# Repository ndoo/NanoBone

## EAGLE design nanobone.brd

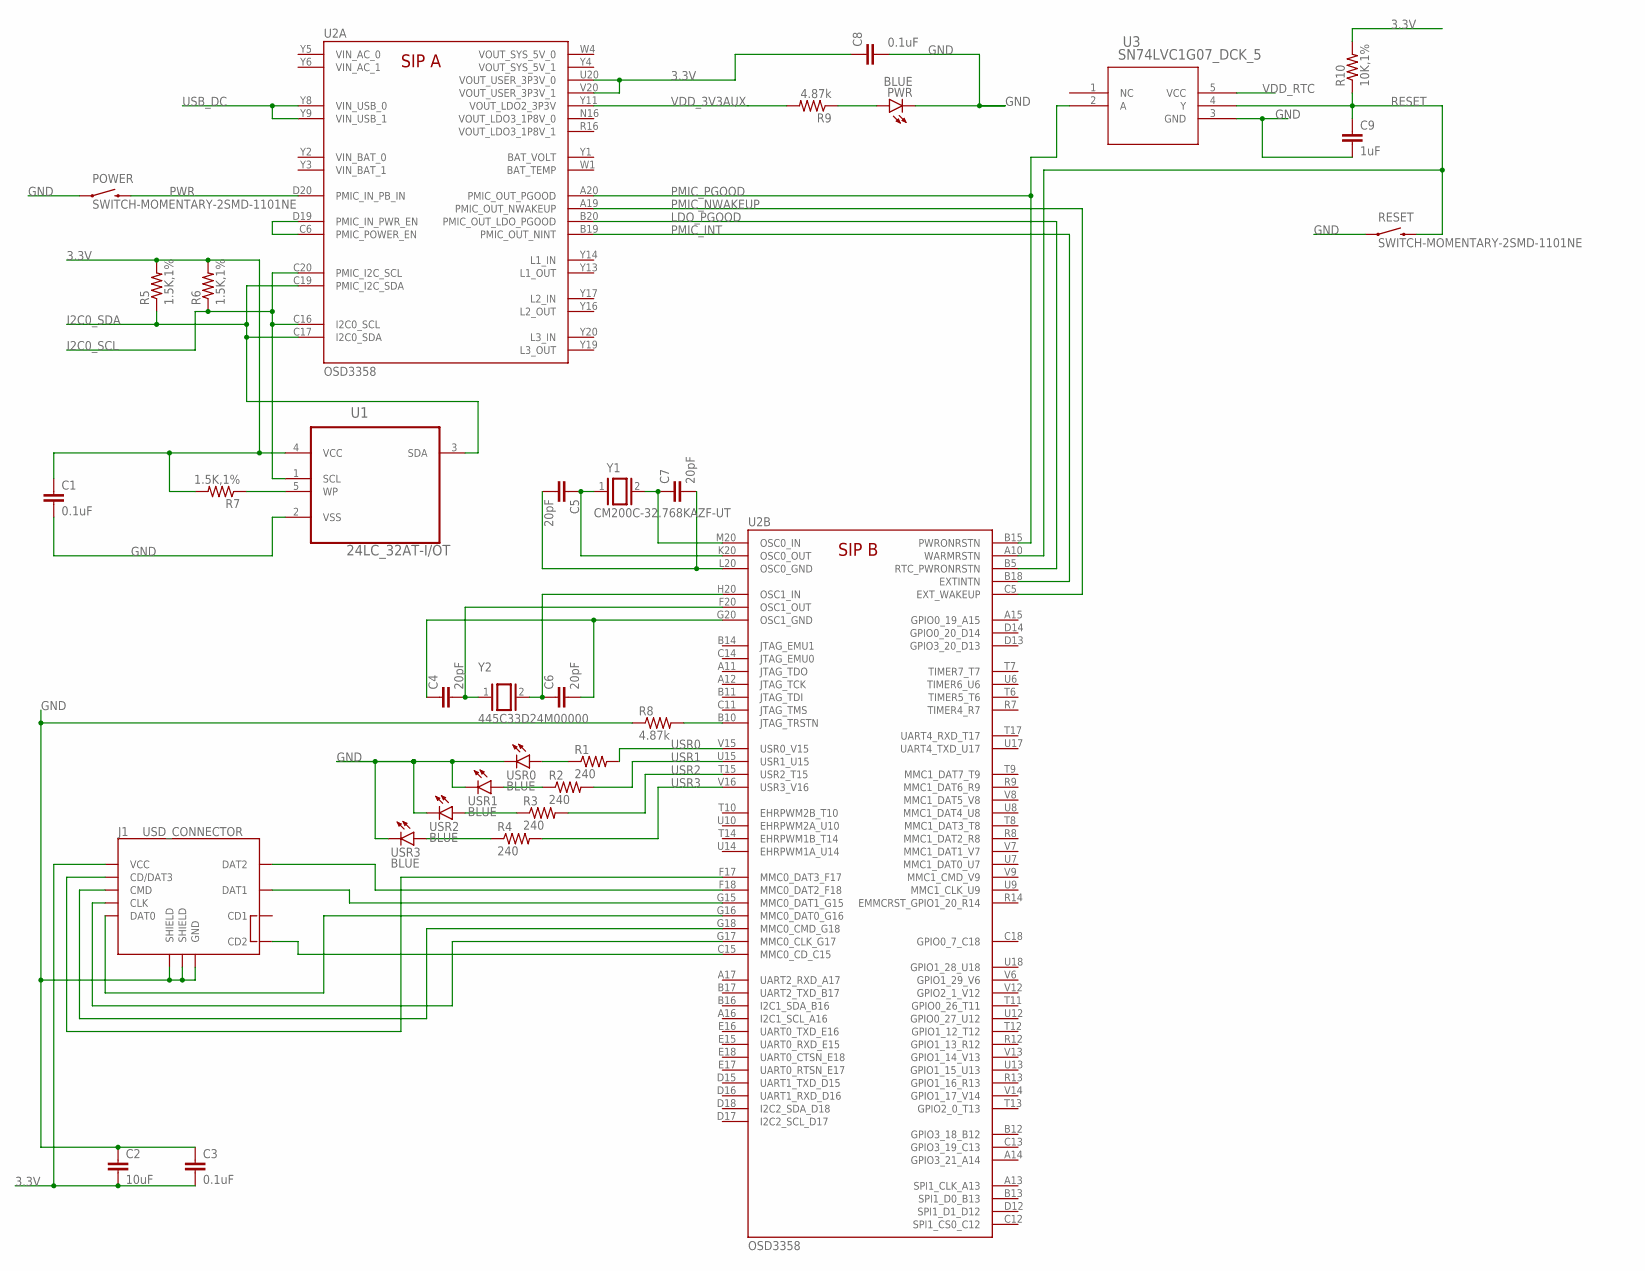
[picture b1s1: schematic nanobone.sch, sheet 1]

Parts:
C1, C3, C8: 0.1uF; 0402-CAP
C2: 10uF; 0805
C4, C5, C6, C7: 20pF; 0402-CAP
C9: 1uF; 0402-CAP
J1: USD_CONNECTOR; MICRO-SD-SOCKET-PP
POWER: SWITCH-MOMENTARY-2SMD-1101NE; TACTILE-SWITCH-1101NE
PWR: BLUE; 0402-LED
R1, R2, R3, R4: 240; 0402-RES
R5, R6, R7: 1.5K,1%; 0402-RES
R8, R9: 4.87k; 0402-RES
R10: 10K,1%; 0402-RES
RESET: SWITCH-MOMENTARY-2SMD-1101NE; TACTILE-SWITCH-1101NE
U1: 24LC_32AT-I/OT; SOT95P290X145-5N
U2: OSD3358
U3: SN74LVC1G07_DCK_5; DCK5
USR0, USR1, USR2, USR3: BLUE; 0402-LED
Y1: CM200C-32.768KAZF-UT
Y2: 445C33D24M00000

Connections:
3.3V: C1.1, C2.2, C3.2, C8.1, J1.VCC, R5.2, R6.2, R7.2, R10.2, U1.4 (VCC), U2.U20 (VOUT_USER_3P3V_0), U2.V20 (VOUT_USER_3P3V_1); also elsewhere on the board
GND: C1.2, C2.1, C3.1, C8.2, C9.2, J1.GND, J1.GND1 (SHIELD), J1.GND3 (SHIELD), POWER.1, PWR.C, R8.1, RESET.1, U1.2 (VSS), U3.3 (GND), USR0.C, USR1.C, USR2.C, USR3.C; also elsewhere on the board
I2C0_SCL: R6.1, U1.1 (SCL), U2.C16 (I2C0_SCL), U2.C20 (PMIC_I2C_SCL)
I2C0_SDA: R5.1, U1.3 (SDA), U2.C17 (I2C0_SDA), U2.C19 (PMIC_I2C_SDA)
LDO_PGOOD: U2.B5 (RTC_PWRONRSTN), U2.B20 (PMIC_OUT_LDO_PGOOD)
unnamed: J1.CLK, U2.G17 (MMC0_CLK_G17)
unnamed: J1.CD/DAT3, U2.F17 (MMC0_DAT3_F17)
unnamed: R8.2, U2.B10 (JTAG_TRSTN)
unnamed: R1.1, USR0.A
unnamed: R2.1, USR1.A
unnamed: R3.1, USR2.A
unnamed: R4.1, USR3.A
unnamed: U2.C6 (PMIC_POWER_EN), U2.D19 (PMIC_IN_PWR_EN)
unnamed: PWR.A, R9.1
unnamed: C7.1, U2.M20 (OSC0_IN), Y1.2
unnamed: C5.1, U2.K20 (OSC0_OUT), Y1.1
unnamed: R7.1, U1.5 (WP)
unnamed: C5.2, C7.2, U2.L20 (OSC0_GND)
unnamed: C6.1, U2.H20 (OSC1_IN), Y2.2
unnamed: C4.2, U2.F20 (OSC1_OUT), Y2.1
unnamed: C4.1, C6.2, U2.G20 (OSC1_GND)
unnamed: J1.DAT1, U2.G15 (MMC0_DAT1_G15)
unnamed: J1.CMD, U2.G18 (MMC0_CMD_G18)
unnamed: J1.CD2, U2.C15 (MMC0_CD_C15)
unnamed: J1.DAT0, U2.G16 (MMC0_DAT0_G16)
NTE: J1.DAT2, U2.F18 (MMC0_DAT2_F18)
PMIC_INT: U2.B18 (EXTINTN), U2.B19 (PMIC_OUT_NINT)
PMIC_NWAKEUP: U2.A19 (PMIC_OUT_NWAKEUP), U2.C5 (EXT_WAKEUP)
PMIC_PGOOD: U2.A20 (PMIC_OUT_PGOOD), U2.B15 (PWRONRSTN), U3.2 (A)
PWR: POWER.2, U2.D20 (PMIC_IN_PB_IN)
RESET: C9.1, R10.1, RESET.2, U2.A10 (WARMRSTN), U3.4 (Y)
USB_DC: U2.Y8 (VIN_USB_0), U2.Y9 (VIN_USB_1); also elsewhere on the board
USR0: R1.2, U2.V15 (USR0_V15)
USR1: R2.2, U2.U15 (USR1_U15)
USR2: R3.2, U2.T15 (USR2_T15)
USR3: R4.2, U2.V16 (USR3_V16)
VDD_3V3AUX: R9.2, U2.Y11 (VOUT_LDO2_3P3V)
VDD_RTC: U3.5 (VCC); also elsewhere on the board
VIN_AC_0: U2.Y5 (VIN_AC_0)
VIN_AC_1: U2.Y6 (VIN_AC_1)
VIN_BAT_0: U2.Y2 (VIN_BAT_0)
VIN_BAT_1: U2.Y3 (VIN_BAT_1)
VOUT_LDO3_1P8V_0: U2.N16 (VOUT_LDO3_1P8V_0)
VOUT_LDO3_1P8V_1: U2.R16 (VOUT_LDO3_1P8V_1)
VOUT_SYS_5V_0: U2.W4 (VOUT_SYS_5V_0)
VOUT_SYS_5V_1: U2.Y4 (VOUT_SYS_5V_1)

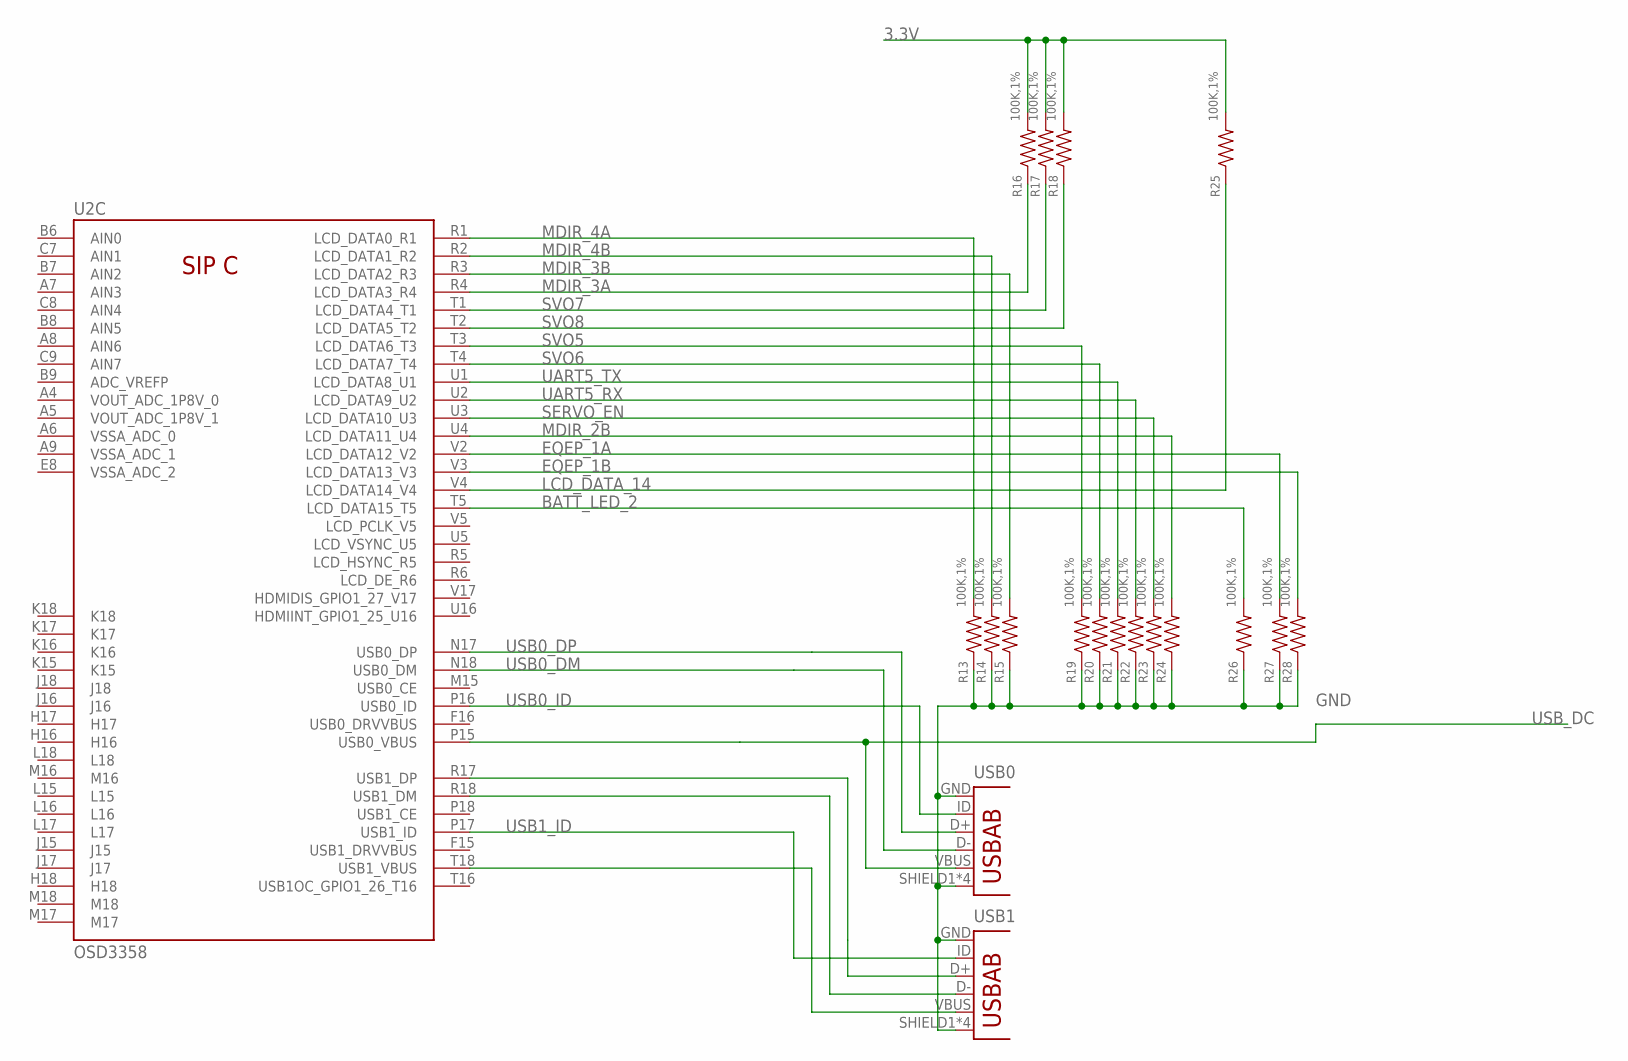
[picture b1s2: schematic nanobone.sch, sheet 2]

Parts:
R13, R14, R15, R16, R17, R18, R19, R20, R21, R22, R23, R24, R25, R26, R27, R28: 100K,1%; 0402-RES
U2: OSD3358
USB0, USB1: USB-AB; USB-AB-MICRO-SMD

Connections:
3.3V: R16.2, R17.2, R18.2, R25.2; also elsewhere on the board
BATT_LED_2: R26.2, U2.T5 (LCD_DATA15_T5)
EQEP_1A: R27.2, U2.V2 (LCD_DATA12_V2)
EQEP_1B: R28.2, U2.V3 (LCD_DATA13_V3)
GND: R13.1, R14.1, R15.1, R19.1, R20.1, R21.1, R22.1, R23.1, R24.1, R26.1, R27.1, R28.1, USB0.GND, USB0.SHIELD1 (SHIELD), USB0.SHIELD2 (SHIELD), USB0.SHIELD3 (SHIELD), USB0.SHIELD4 (SHIELD), USB1.GND, USB1.SHIELD1 (SHIELD), USB1.SHIELD2 (SHIELD), USB1.SHIELD3 (SHIELD), USB1.SHIELD4 (SHIELD); also elsewhere on the board
LCD_DATA_14: R25.1, U2.V4 (LCD_DATA14_V4)
MDIR_2B: R24.2, U2.U4 (LCD_DATA11_U4)
MDIR_3A: R16.1, U2.R4 (LCD_DATA3_R4)
MDIR_3B: R15.2, U2.R3 (LCD_DATA2_R3)
MDIR_4A: R13.2, U2.R1 (LCD_DATA0_R1)
MDIR_4B: R14.2, U2.R2 (LCD_DATA1_R2)
unnamed: U2.R17 (USB1_DP), USB1.D+
unnamed: U2.R18 (USB1_DM), USB1.D-
unnamed: U2.T18 (USB1_VBUS), USB1.VBUS
SERVO_EN: R23.2, U2.U3 (LCD_DATA10_U3)
SVO5: R19.2, U2.T3 (LCD_DATA6_T3)
SVO6: R20.2, U2.T4 (LCD_DATA7_T4)
SVO7: R17.1, U2.T1 (LCD_DATA4_T1)
SVO8: R18.1, U2.T2 (LCD_DATA5_T2)
UART5_RX: R22.2, U2.U2 (LCD_DATA9_U2)
UART5_TX: R21.2, U2.U1 (LCD_DATA8_U1)
USB0_DM: U2.N18 (USB0_DM), USB0.D-
USB0_DP: U2.N17 (USB0_DP), USB0.D+
USB0_ID: U2.P16 (USB0_ID), USB0.ID (USBID)
USB1_ID: U2.P17 (USB1_ID), USB1.ID (USBID)
USB_DC: U2.P15 (USB0_VBUS), USB0.VBUS; also elsewhere on the board
VIN_AC_0: U2.Y5 (VIN_AC_0)
VIN_AC_1: U2.Y6 (VIN_AC_1)
VIN_BAT_0: U2.Y2 (VIN_BAT_0)
VIN_BAT_1: U2.Y3 (VIN_BAT_1)
VOUT_LDO3_1P8V_0: U2.N16 (VOUT_LDO3_1P8V_0)
VOUT_LDO3_1P8V_1: U2.R16 (VOUT_LDO3_1P8V_1)
VOUT_SYS_5V_0: U2.W4 (VOUT_SYS_5V_0)
VOUT_SYS_5V_1: U2.Y4 (VOUT_SYS_5V_1)

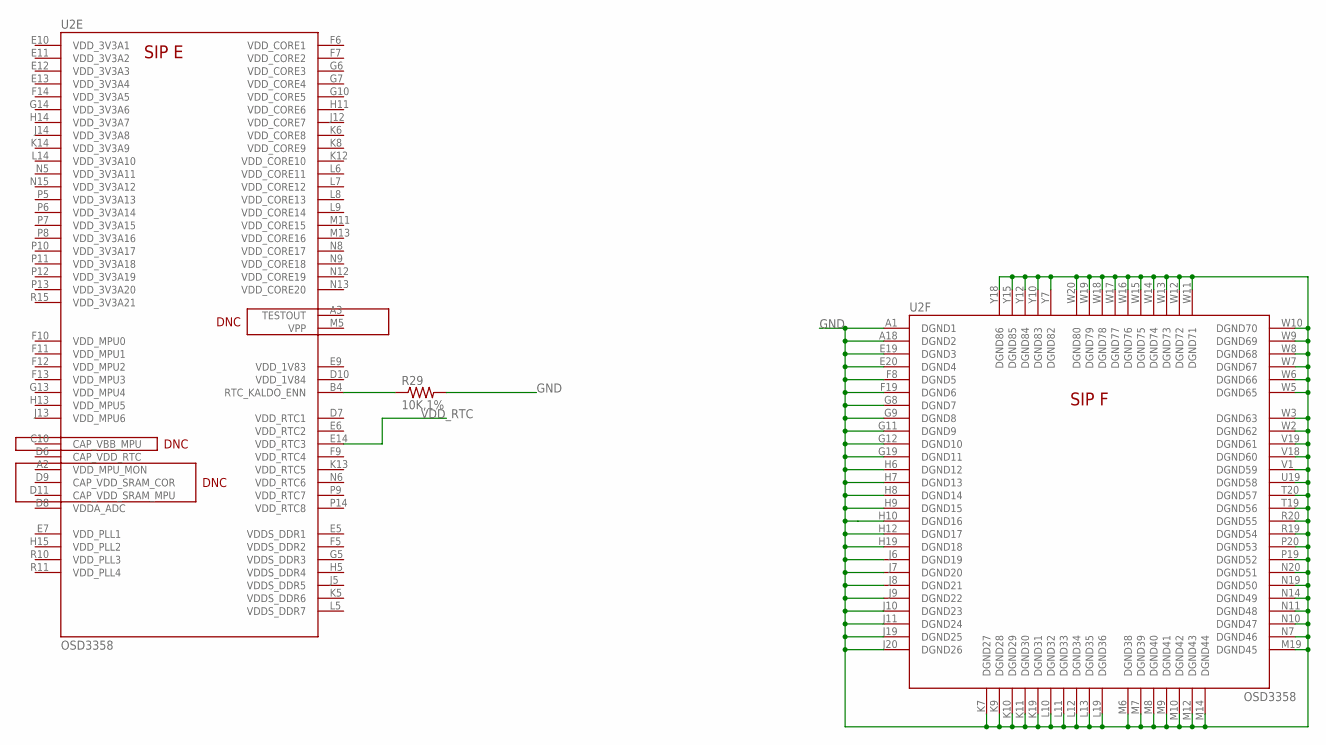
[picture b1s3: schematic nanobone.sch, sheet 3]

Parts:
R29: 10K,1%; 0402-RES
U2: OSD3358

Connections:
GND: R29.2, U2.A1 (DGND1), U2.A18 (DGND2), U2.E19 (DGND3), U2.E20 (DGND4), U2.F8 (DGND5), U2.F19 (DGND6), U2.G8 (DGND7), U2.G9 (DGND8), U2.G11 (DGND9), U2.G12 (DGND10), U2.G19 (DGND11), U2.H6 (DGND12), U2.H7 (DGND13), U2.H8 (DGND14), U2.H9 (DGND15), U2.H10 (DGND16), U2.H12 (DGND17), U2.H19 (DGND18), U2.J6 (DGND19), U2.J7 (DGND20), U2.J8 (DGND21), U2.J9 (DGND22), U2.J10 (DGND23), U2.J11 (DGND24), U2.J19 (DGND25), U2.J20 (DGND26), U2.K7 (DGND27), U2.K9 (DGND28), U2.K10 (DGND29), U2.K11 (DGND30), U2.K19 (DGND31), U2.L10 (DGND32), U2.L11 (DGND33), U2.L12 (DGND34), U2.L13 (DGND35), U2.L19 (DGND36), U2.M6 (DGND38), U2.M7 (DGND39), U2.M8 (DGND40), U2.M9 (DGND41), U2.M10 (DGND42), U2.M12 (DGND43), U2.M14 (DGND44), U2.M19 (DGND45), U2.N7 (DGND46), U2.N10 (DGND47), U2.N11 (DGND48), U2.N14 (DGND49), U2.N19 (DGND50), U2.N20 (DGND51), U2.P19 (DGND52), U2.P20 (DGND53), U2.R19 (DGND54), U2.R20 (DGND55), U2.T19 (DGND56), U2.T20 (DGND57), U2.U19 (DGND58), U2.V1 (DGND59), U2.V18 (DGND60), U2.V19 (DGND61), U2.W2 (DGND62), U2.W3 (DGND63), U2.W5 (DGND65), U2.W6 (DGND66), U2.W7 (DGND67), U2.W8 (DGND68), U2.W9 (DGND69), U2.W10 (DGND70), U2.W11 (DGND71), U2.W12 (DGND72), U2.W13 (DGND73), U2.W14 (DGND74), U2.W15 (DGND75), U2.W16 (DGND76), U2.W17 (DGND77), U2.W18 (DGND78), U2.W19 (DGND79), U2.W20 (DGND80), U2.Y7 (DGND82), U2.Y10 (DGND83), U2.Y12 (DGND84), U2.Y15 (DGND85), U2.Y18 (DGND86); also elsewhere on the board
unnamed: R29.1, U2.B4 (RTC_KALDO_ENN)
VDD_RTC: U2.E14 (VDD_RTC3); also elsewhere on the board
VIN_AC_0: U2.Y5 (VIN_AC_0)
VIN_AC_1: U2.Y6 (VIN_AC_1)
VIN_BAT_0: U2.Y2 (VIN_BAT_0)
VIN_BAT_1: U2.Y3 (VIN_BAT_1)
VOUT_LDO3_1P8V_0: U2.N16 (VOUT_LDO3_1P8V_0)
VOUT_LDO3_1P8V_1: U2.R16 (VOUT_LDO3_1P8V_1)
VOUT_SYS_5V_0: U2.W4 (VOUT_SYS_5V_0)
VOUT_SYS_5V_1: U2.Y4 (VOUT_SYS_5V_1)

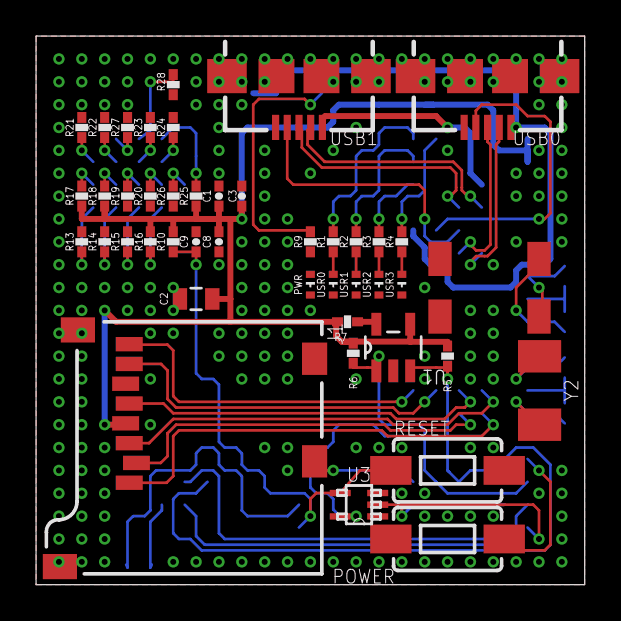
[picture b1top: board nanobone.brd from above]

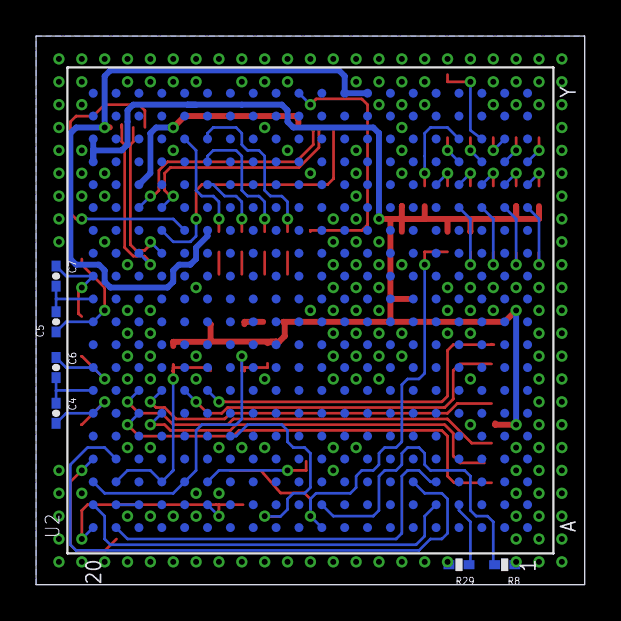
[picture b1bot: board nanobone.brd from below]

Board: 2 copper layers, 30.5 x 30.5 mm, 51 parts (7 on the bottom side), 62 nets.

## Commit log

2016-05-27 Reduce size (WIP) and change DRU for Seeed Studio tolerances
2016-05-27 Ignore EAGLE .lck files
2016-05-27 Route XTAL
2016-05-27 Add the missing 2xµUSB OTG ports, cleanup
2016-06-07 Added AR8035 PHY (layout not done), reduced size
2016-06-07 Rename to differentiate from PocketBone project as objectives have diverged
2016-06-07 Removed AR8035 due to lack of space and routing issues. Centered crystals in pocketbone.lbr and renamed to nanobone.lbr
2016-06-08 Smash names and cleaned up for visibility
2016-06-11 Remove PHY nets from schematic. Tie all DGND to GND plane. Improve USB differential pair isolation.
2016-06-11 Add 0402 SMD LED
2016-06-11 Cleaned layout further, added USB1_ID, added user LEDs
2016-06-12 Fix µSD trace ground plane surround
2016-06-25 Fix USB_DC leftover trace. Define 6mil isolation for pour polygons.

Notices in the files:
parts and their libraries:
SparkFun-Electromechanical: Licensing: Creative Commons ShareAlike 4.0 International - https://creativecommons.org/licenses/by-sa/4.0
